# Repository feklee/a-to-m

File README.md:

Introduction
============

A-to-M is an experimental construction system: Atoms (*A*) are
assembled *to* form molecules (*M*).

A molecule is powered with a USB-C adapter. This adapter is also used
to program individual atoms.

Design guidelines
=================

For areas without solder mask, don’t use components smaller than 0603
and don’t put traces too close. A clearance of 0.35 mm is good.

MiniCore
========

For a good experience, i.e. fast power up of an atom upon connection,
install [MiniCore][1] as boot loader.

Examples
========

Atomic tree
-----------

Sequencer
---------

[][2]  
[Video][2]

License
=======

Except where noted otherwise, files are licensed under the WTFPL.

Copyright © 2020 [Felix E. Klee](felix.klee@inka.de)

This work is free. You can redistribute it and/or modify it under the
terms of the Do What The Fuck You Want To Public License, Version 2,
as published by Sam Hocevar. See the COPYING file for more details.

[1]: https://github.com/MCUdude/MiniCore
[2]: https://archive.org/details/a-to-m-sequencer

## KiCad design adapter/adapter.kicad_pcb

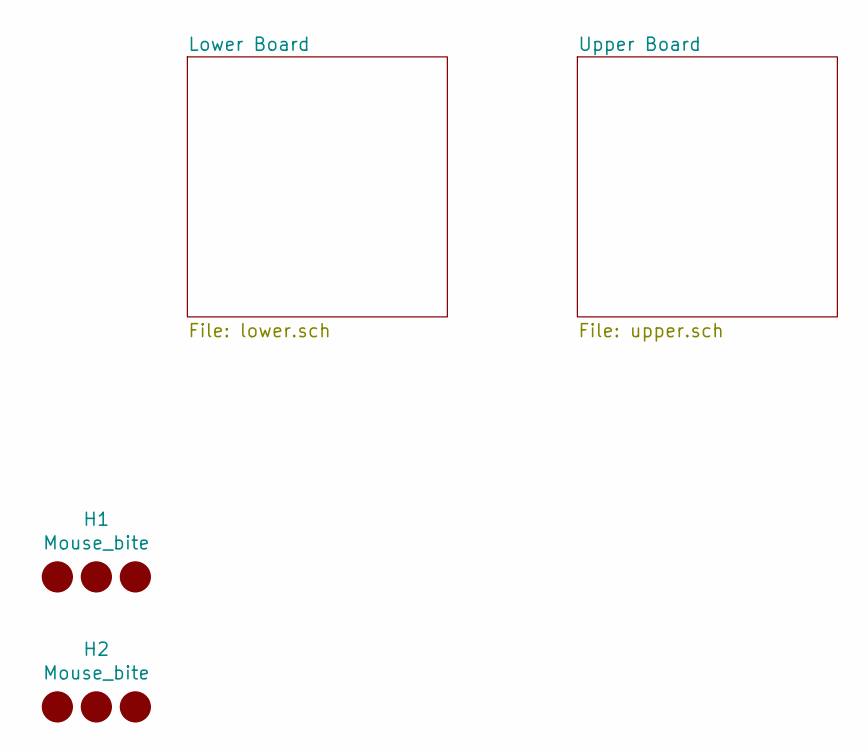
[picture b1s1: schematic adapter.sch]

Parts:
H1, H2: Mouse_bite; single_sided_tab_5mm

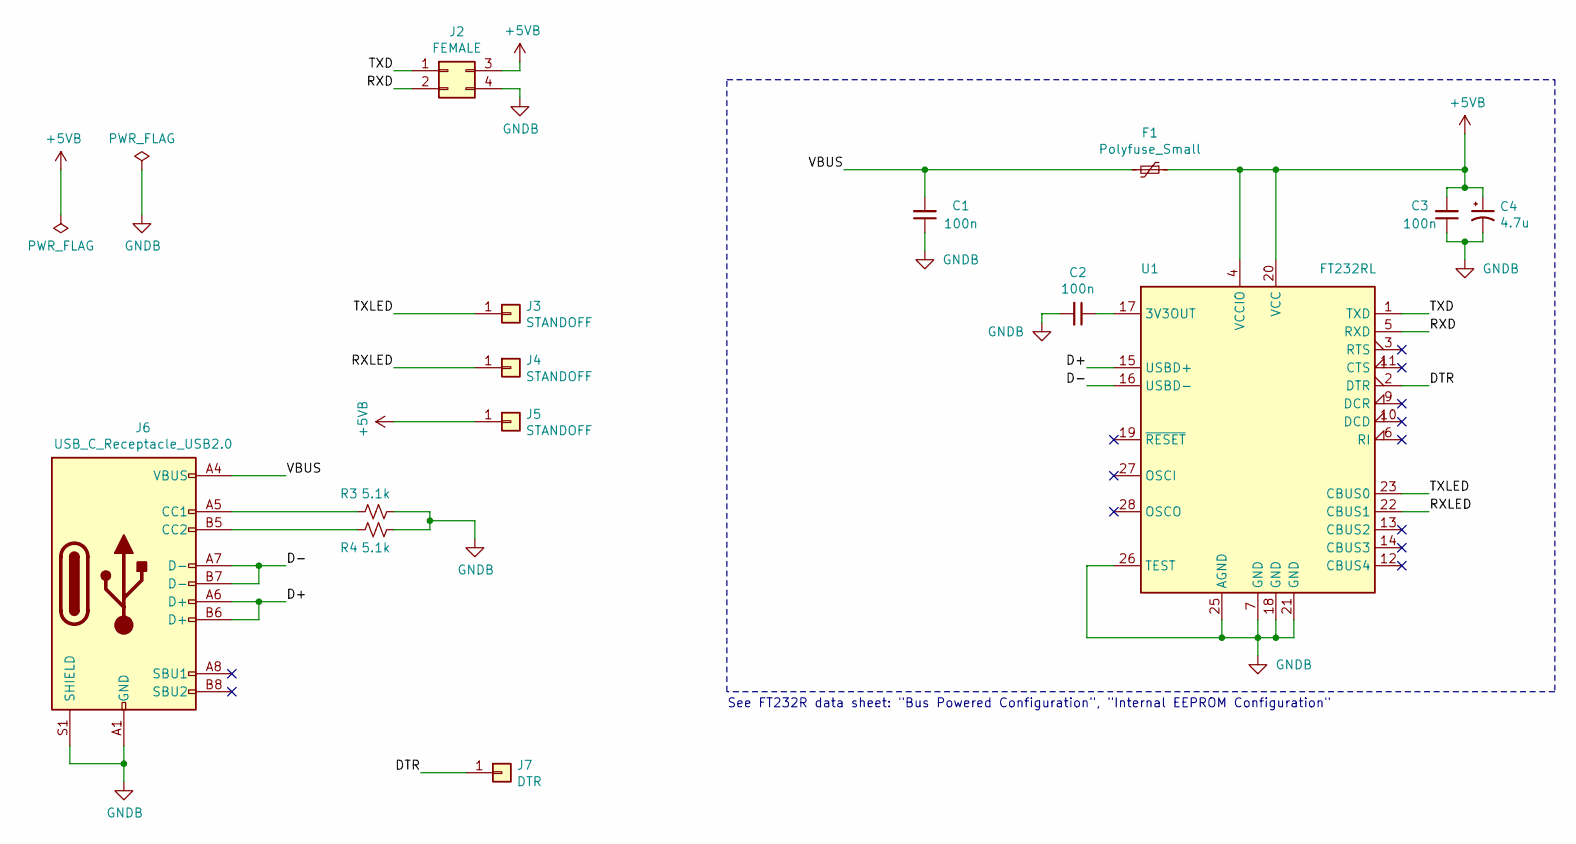
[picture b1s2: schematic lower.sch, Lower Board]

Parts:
C1, C2, C3: 100n; C_0805_2012Metric_Pad1.15x1.40mm_HandSolder
C4: 4.7u; C_0805_2012Metric_Pad1.15x1.40mm_HandSolder
F1: Polyfuse_Small; Fuse_1206_3216Metric_Pad1.42x1.75mm_HandSolder
J2: FEMALE; PinSocket_2x02_P2.54mm_Horizontal
J3, J4, J5: STANDOFF; MountingHole_2.2mm_M2_Pad_Via
J6: USB_C_Receptacle_USB2.0; SOFNG_MC-311D
J7: DTR; PinHeader_1x01_P2.54mm_Vertical
R3, R4: 5.1k; R_0805_2012Metric_Pad1.20x1.40mm_HandSolder
U1: FT232RL; SSOP-28_5.3x10.2mm_P0.65mm

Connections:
+5VB: C3.2, C4.1, F1.1, J2.3, J5.1, U1.4 (VCCIO), U1.20 (VCC)
/Lower Board/D+: J6.A6 (D+), J6.B6 (D+), U1.15 (USBD+)
/Lower Board/D-: J6.A7 (D-), J6.B7 (D-), U1.16 (USBD-)
/Lower Board/DTR: J7.1, U1.2 (DTR)
/Lower Board/RXD: J2.2, U1.5 (RXD)
/Lower Board/RXLED: J4.1, U1.22 (CBUS1)
/Lower Board/TXD: J2.1, U1.1 (TXD)
/Lower Board/TXLED: J3.1, U1.23 (CBUS0)
/Lower Board/VBUS: C1.2, F1.2, J6.A4 (VBUS), J6.A9 (VBUS), J6.B4 (VBUS), J6.B9 (VBUS)
GNDB: C1.1, C2.2, C3.1, C4.2, J2.4, J6.A1 (GND), J6.A12 (GND), J6.B1 (GND), J6.B12 (GND), J6.S1 (SHIELD), R3.1, R4.1, U1.7 (GND), U1.18 (GND), U1.21 (GND), U1.25 (AGND), U1.26 (TEST)
unnamed: C2.1, U1.17 (3V3OUT)
unnamed: J6.A5 (CC1), R3.2
unnamed: J6.B5 (CC2), R4.2

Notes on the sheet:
See FT232R data sheet: "Bus Powered Configuration", "Internal EEPROM Configuration"

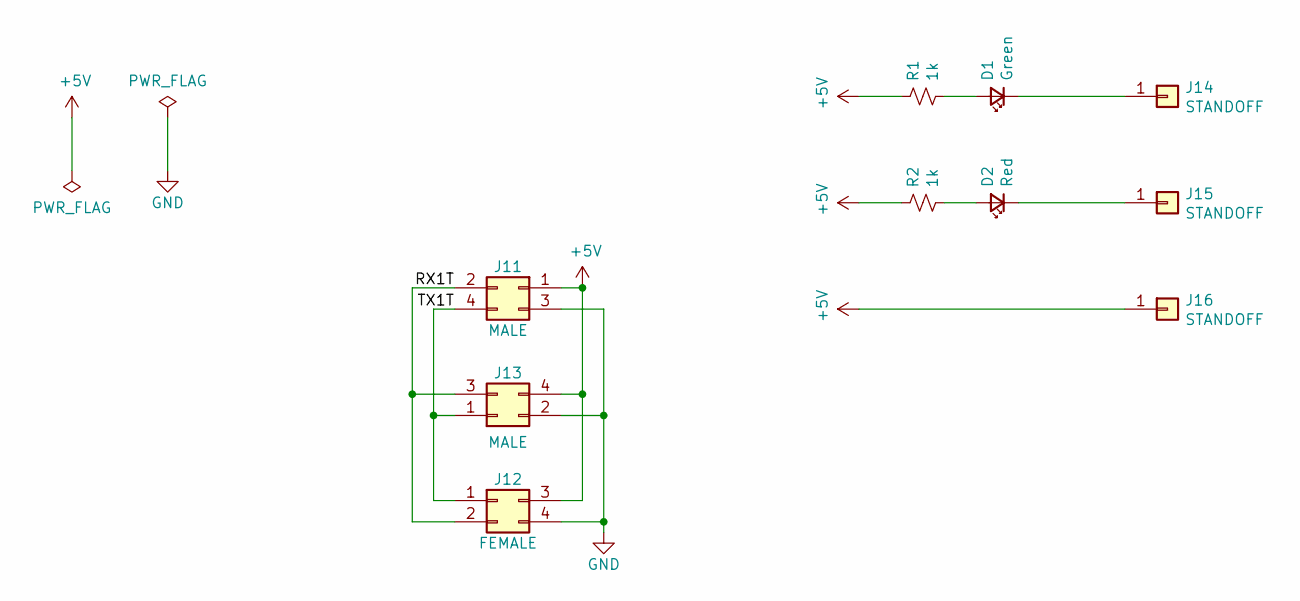
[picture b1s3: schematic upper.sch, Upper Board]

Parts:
D1: Green; LED_0805_2012Metric_Pad1.15x1.40mm_HandSolder
D2: Red; LED_0805_2012Metric_Pad1.15x1.40mm_HandSolder
J11, J13: MALE; PinHeader_2x02_P2.54mm_Horizontal
J12: FEMALE; PinSocket_2x02_P2.54mm_Horizontal
J14, J15, J16: STANDOFF; MountingHole_2.2mm_M2_Pad_Via
R1, R2: 1k; R_0805_2012Metric_Pad1.20x1.40mm_HandSolder

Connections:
+5V: J11.1, J12.3, J13.4, J16.1, R1.1, R2.1
/Upper Board/RX1T: J11.2, J12.2, J13.3
/Upper Board/TX1T: J11.4, J12.1, J13.1
GND: J11.3, J12.4, J13.2
unnamed: D1.1 (K), J14.1
unnamed: D1.2 (A), R1.2
unnamed: D2.1 (K), J15.1
unnamed: D2.2 (A), R2.2

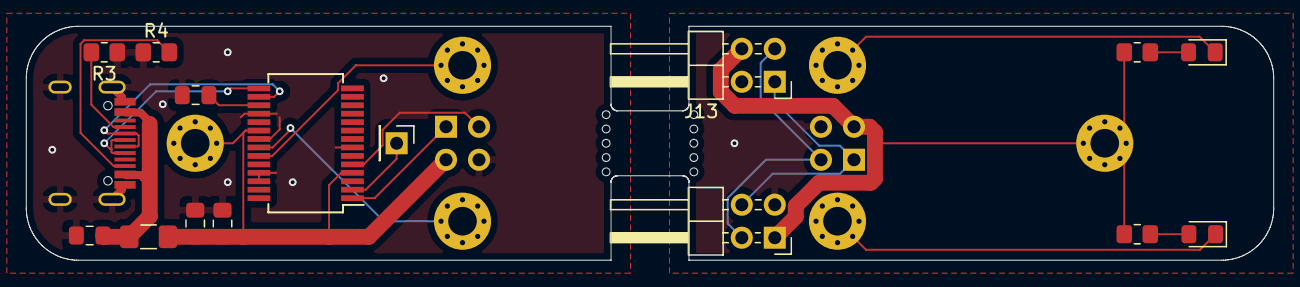
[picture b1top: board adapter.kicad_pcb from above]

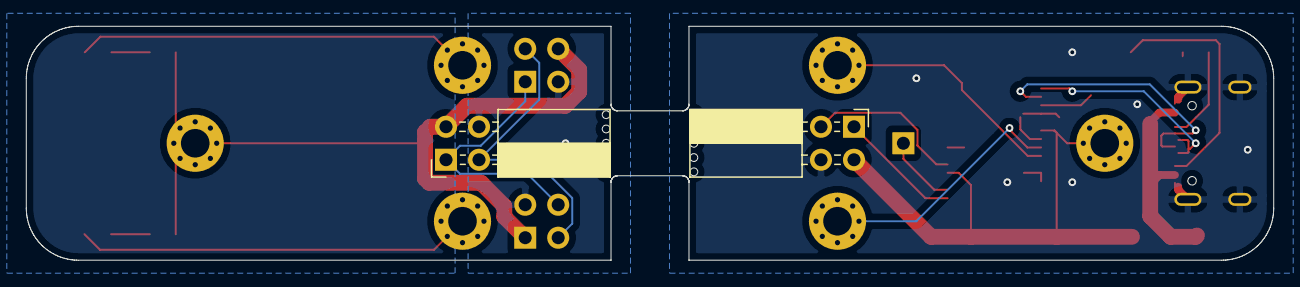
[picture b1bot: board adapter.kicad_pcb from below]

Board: 2 copper layers, 96.0 x 18.0 mm, 26 parts (2 on the bottom side), 21 nets.

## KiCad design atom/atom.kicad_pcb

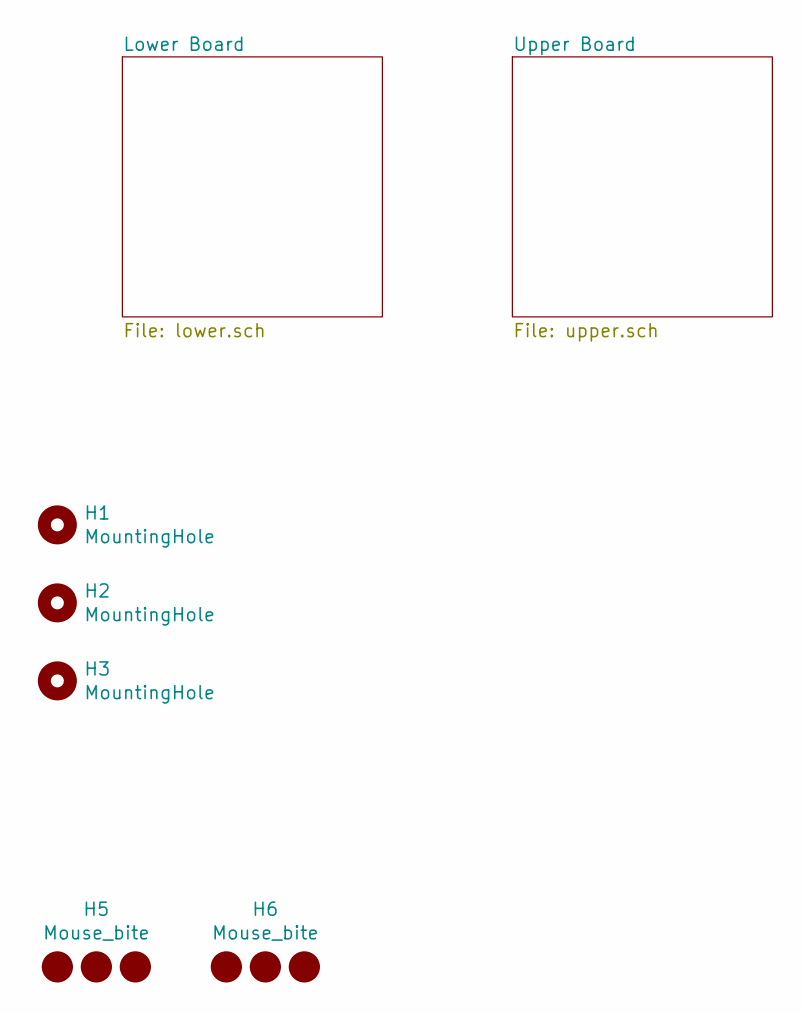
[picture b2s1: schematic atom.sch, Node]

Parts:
H1, H2, H3: MountingHole; JLCPCB-tooling-hole; JLCPCB BOM False
H5, H6: Mouse_bite; single_sided_tab_5mm; JLCPCB BOM False

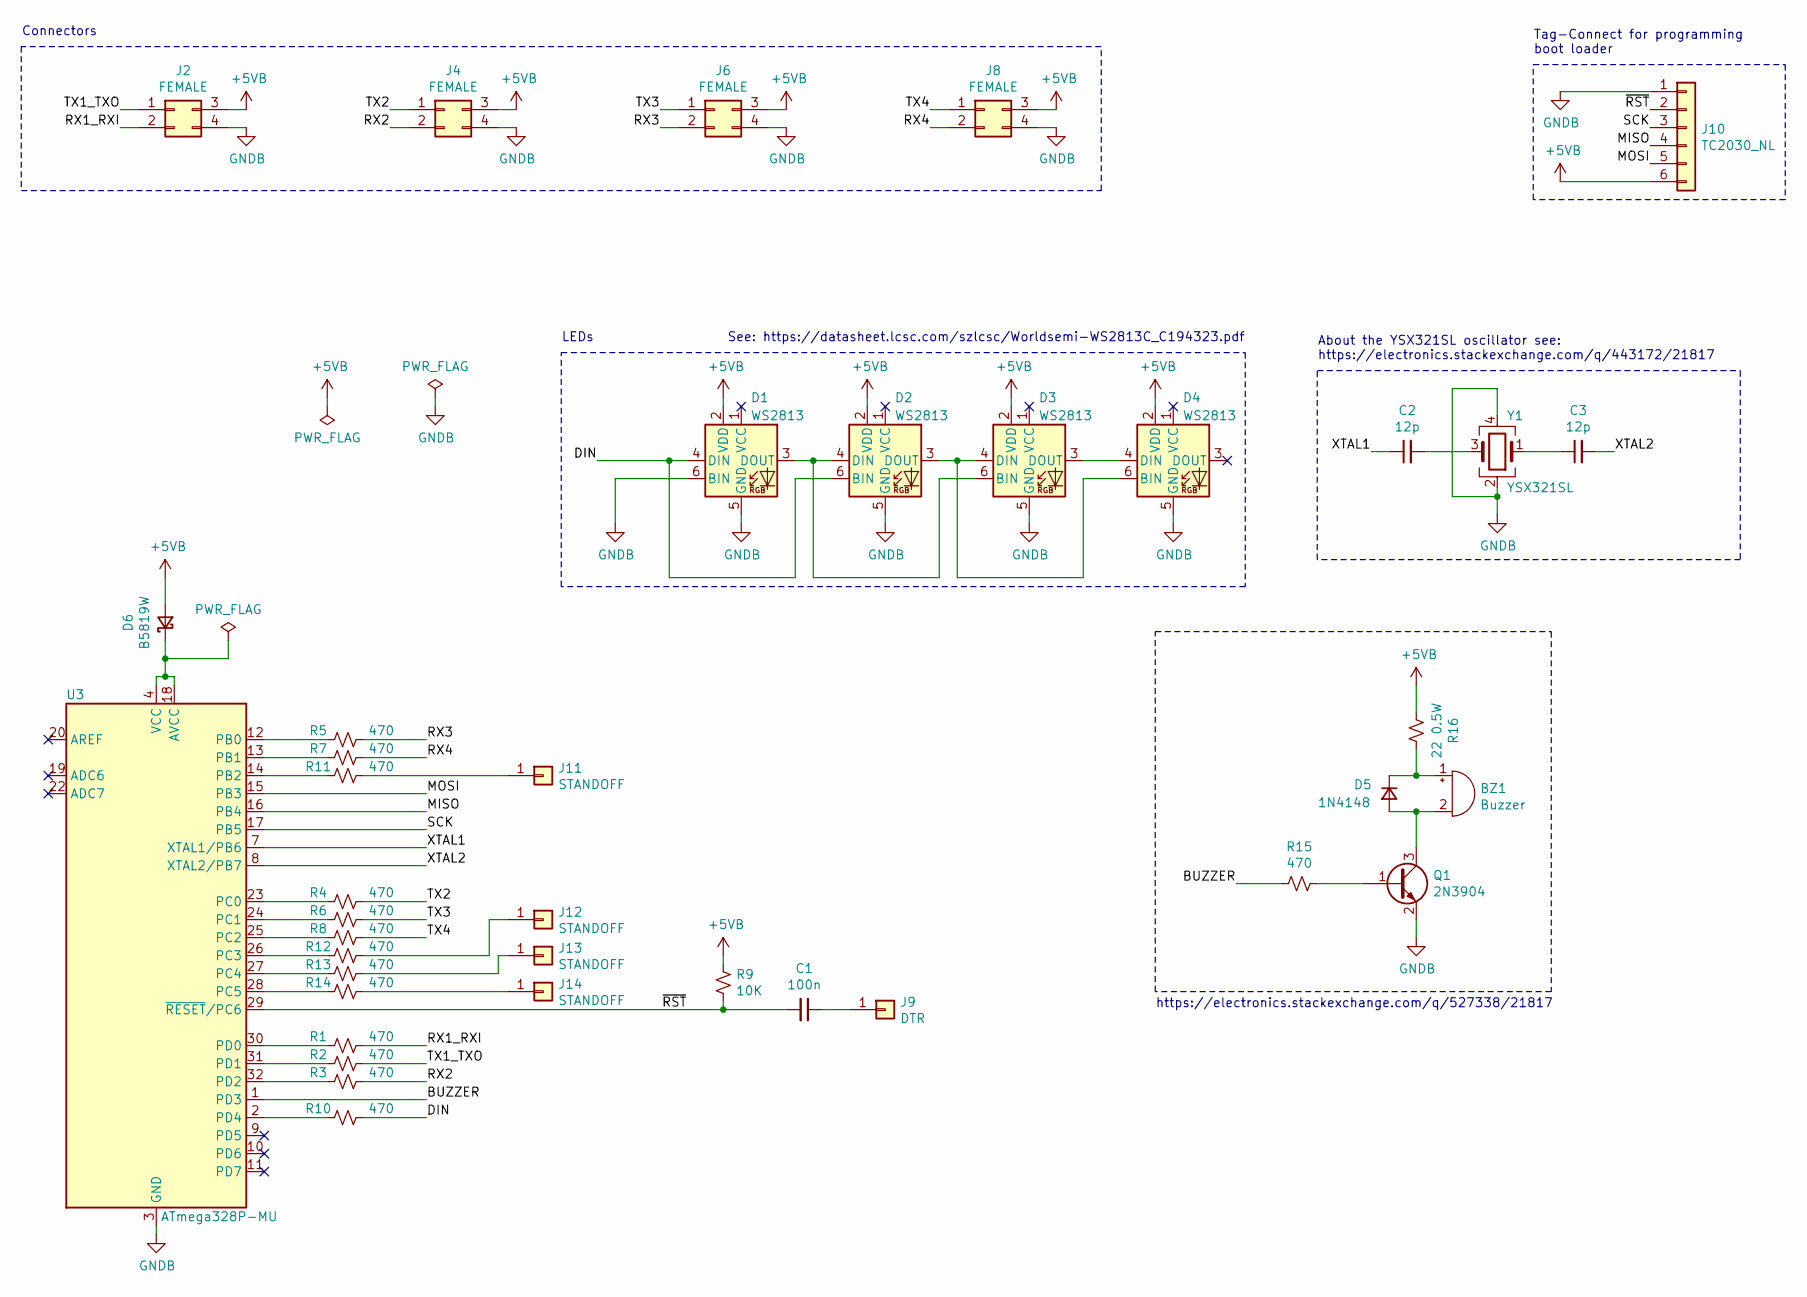
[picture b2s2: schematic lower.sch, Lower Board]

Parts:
BZ1: Buzzer; MLT-5020; MPN MLT-5020; LCSC Part C94598
C1: 100n; C_0402_1005Metric; MPN CL05B104KO5NNNC; LCSC Part C1525
C2, C3: 12p; C_0402_1005Metric; MPN 0402CG120J500NT; LCSC Part C1547
D1, D2, D3, D4: WS2813; bottom-leaf; MPN WS2813C; LCSC Part C194323
D5: 1N4148; D_SOD-323; MPN 1N4148WS-7-F; LCSC Part C60580
D6: B5819W; D_SOD-123
J2, J4, J6, J8: FEMALE; PinSocket_2x02_P2.54mm_Horizontal; MPN A2541HWR-2x2P; LCSC Part C239353
J9: DTR; PinHeader_1x01_P2.54mm_Vertical; JLCPCB BOM False
J10: TC2030_NL; Tag-Connect_TC2030-IDC-NL_2x03_P1.27mm_Vertical; JLCPCB BOM False
J11, J12, J13, J14: STANDOFF; MountingHole_2.2mm_M2_Pad_Via; JLCPCB BOM False
Q1: 2N3904; SOT-23; MPN PMBT3904,215; LCSC Part C8667
R1, R2, R3, R4, R5, R6, R7, R8, R10, R11, R12, R13, R14, R15: 470; R_0402_1005Metric; MPN 0402WGF4700TCE; LCSC Part C25117
R9: 10K; R_0402_1005Metric; MPN 0402WGF1002TCE; LCSC Part C25744
R16: 22 0.5W; R_2010_5025Metric; MPN 2010W2F220JT4S; LCSC Part C70404
U3: ATmega328P-MU; QFN-32-1EP_5x5mm_P0.5mm_EP3.1x3.1mm; MPN ATMEGA328P-MU; LCSC Part C783592
Y1: YSX321SL; MPN X322516MOB4SI; LCSC Part C12668

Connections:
+5VB: D1.2 (VDD), D2.2 (VDD), D3.2 (VDD), D4.2 (VDD), D6.2 (A), J2.3, J4.3, J6.3, J8.3, J10.6, R9.1, R16.2
/Lower Board/BUZZER: R15.2, U3.1 (PD3)
/Lower Board/DIN: D1.4 (DIN), D2.6 (BIN), R10.1
/Lower Board/MISO: J10.4, U3.16 (PB4)
/Lower Board/MOSI: J10.5, U3.15 (PB3)
/Lower Board/RX1_RXI: J2.2, R1.1
/Lower Board/RX2: J4.2, R3.1
/Lower Board/RX3: J6.2, R5.1
/Lower Board/RX4: J8.2, R7.1
/Lower Board/SCK: J10.3, U3.17 (PB5)
/Lower Board/TX1_TXO: J2.1, R2.1
/Lower Board/TX2: J4.1, R4.1
/Lower Board/TX3: J6.1, R6.1
/Lower Board/TX4: J8.1, R8.1
/Lower Board/XTAL1: C2.1, U3.7 (XTAL1/PB6)
/Lower Board/XTAL2: C3.2, U3.8 (XTAL2/PB7)
/Lower Board/~RST: C1.2, J10.2, R9.2, U3.29 (~RESET~/PC6)
GNDB: D1.5 (GND), D1.6 (BIN), D2.5 (GND), D3.5 (GND), D4.5 (GND), J2.4, J4.4, J6.4, J8.4, J10.1, Q1.2 (E), U3.3 (GND), U3.5 (GND), U3.21 (GND), U3.33 (GND), Y1.2, Y1.4
unnamed: BZ1.1 (-), D5.1 (K), R16.1
unnamed: BZ1.2 (+), D5.2 (A), Q1.3 (C)
unnamed: C1.1, J9.1
unnamed: C2.2, Y1.3
unnamed: C3.1, Y1.1
unnamed: D1.3 (DOUT), D2.4 (DIN), D3.6 (BIN)
unnamed: D2.3 (DOUT), D3.4 (DIN), D4.6 (BIN)
unnamed: D3.3 (DOUT), D4.4 (DIN)
unnamed: D6.1 (K), U3.4 (VCC), U3.6 (VCC), U3.18 (AVCC)
unnamed: J11.1, R11.1
unnamed: J12.1, R12.1
unnamed: J13.1, R13.1
unnamed: J14.1, R14.1
unnamed: Q1.1 (B), R15.1
unnamed: R1.2, U3.30 (PD0)
unnamed: R2.2, U3.31 (PD1)
unnamed: R3.2, U3.32 (PD2)
unnamed: R4.2, U3.23 (PC0)
unnamed: R5.2, U3.12 (PB0)
unnamed: R6.2, U3.24 (PC1)
unnamed: R7.2, U3.13 (PB1)
unnamed: R8.2, U3.25 (PC2)
unnamed: R10.2, U3.2 (PD4)
unnamed: R11.2, U3.14 (PB2)
unnamed: R12.2, U3.26 (PC3)
unnamed: R13.2, U3.27 (PC4)
unnamed: R14.2, U3.28 (PC5)

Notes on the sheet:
See: https://datasheet.lcsc.com/szlcsc/Worldsemi-WS2813C_C194323.pdf
LEDs
Connectors
About the YSX321SL oscillator see: https://electronics.stackexchange.com/q/443172/21817
Tag-Connect for programming boot loader
https://electronics.stackexchange.com/q/527338/21817

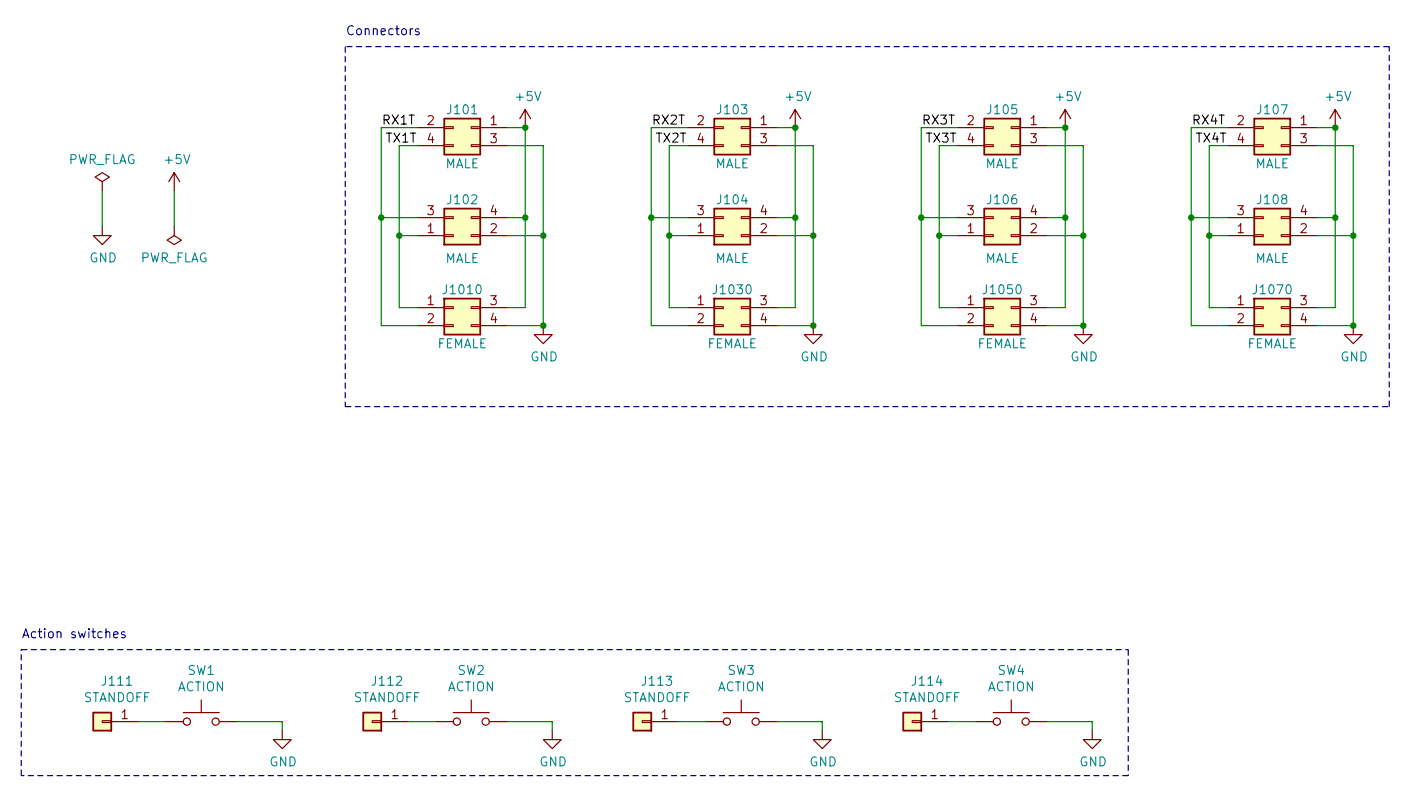
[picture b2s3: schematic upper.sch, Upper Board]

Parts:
J101, J103, J105, J107, J1010, J1030, J1050, J1070: MALE; PinHeader_2x02_P2.54mm_Horizontal; MPN A2541WR-2x2P; LCSC Part C239333
J102, J104, J106, J108: FEMALE; PinSocket_2x02_P2.54mm_Horizontal; MPN A2541HWR-2x2P; LCSC Part C239353
J111, J112, J113, J114: STANDOFF; MountingHole_2.2mm_M2_Pad_Via; JLCPCB BOM False
SW1, SW2, SW3, SW4: ACTION; top-leaf; MPN TS-1187A-B-A-B; LCSC Part C318884

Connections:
+5V: J101.1, J102.3, J103.1, J104.3, J105.1, J106.3, J107.1, J108.3, J1010.4, J1030.4, J1050.4, J1070.4
/Upper Board/RX1T: J101.2, J102.2, J1010.3
/Upper Board/RX2T: J103.2, J104.2, J1030.3
/Upper Board/RX3T: J105.2, J106.2, J1050.3
/Upper Board/RX4T: J107.2, J108.2, J1070.3
/Upper Board/TX1T: J101.4, J102.1, J1010.1
/Upper Board/TX2T: J103.4, J104.1, J1030.1
/Upper Board/TX3T: J105.4, J106.1, J1050.1
/Upper Board/TX4T: J107.4, J108.1, J1070.1
GND: J101.3, J102.4, J103.3, J104.4, J105.3, J106.4, J107.3, J108.4, J1010.2, J1030.2, J1050.2, J1070.2, SW1.2, SW2.2, SW3.2, SW4.2
unnamed: J111.1, SW1.1
unnamed: J112.1, SW2.1
unnamed: J113.1, SW3.1
unnamed: J114.1, SW4.1

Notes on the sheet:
Action switches
Connectors

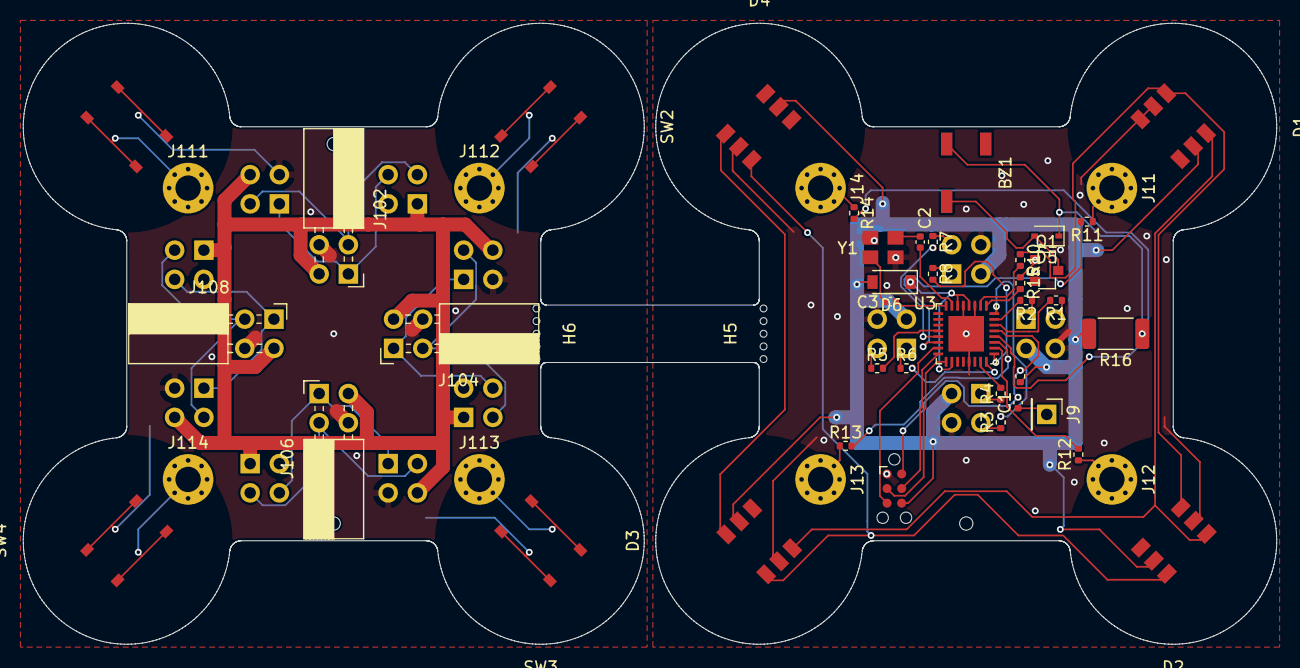
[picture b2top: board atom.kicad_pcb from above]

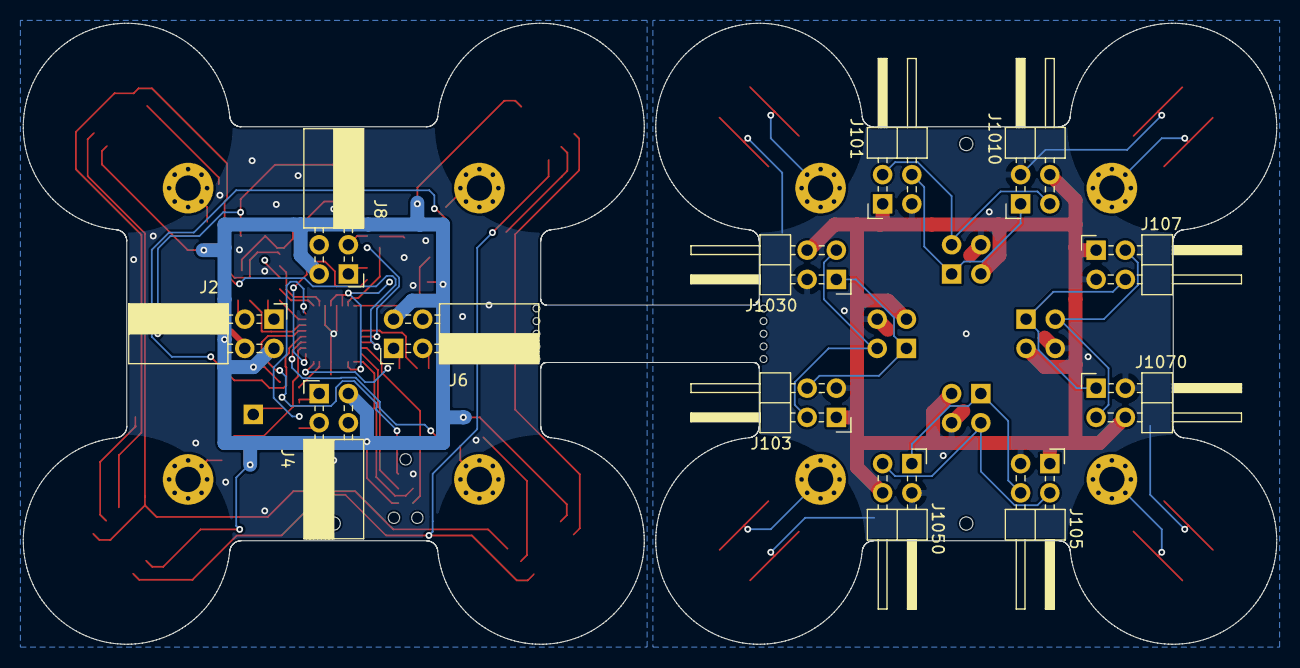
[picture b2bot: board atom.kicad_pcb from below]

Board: 2 copper layers, 109.0 x 54.0 mm, 64 parts (12 on the bottom side), 59 nets.

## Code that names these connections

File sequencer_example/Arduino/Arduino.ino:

#include <FastLED.h>
#include <ezButton.h>

constexpr uint8_t buttonPinNos[] = {
  10, // PB2
  17, // PC3
  18, // PC4
  19 // PC5
};

// This code is for RX and TX not being crossed over. (design bug in
// the board, but fixed since)
constexpr uint8_t communicationPinNos[] = {
  0, // RX1 = PD0 = PCINT16
  2, // RX2 = PD2 = PCINT18
  8, // RX3 = PB0 = PCINT0
  9 // RX4 = PB1 = PCINT1
};

constexpr uint8_t speakerPinNo = 3;

#define LED_PIN     4
#define NUM_LEDS    4
#define BRIGHTNESS  255
#define LED_TYPE    WS2813
#define COLOR_ORDER GRB
CRGB leds[NUM_LEDS];
uint8_t hues[NUM_LEDS];
volatile bool pulseHasBeenReceived = false;
volatile uint8_t commPinThatReceivedPulse;

bool waitingForMultiButtonRelease = false;

constexpr uint8_t noOfDurations = 3;
uint16_t durations[noOfDurations] = { // in ms
  125,
  250,
  375
};
int8_t selectedDurationIndex = 1;

constexpr uint8_t noOfNotes = 14;
uint16_t frequencies[noOfNotes] = {
  2093, // C7
  2349, // D7
  2637, // E7
  2794, // F7
  3136, // G7
  3520, // A7
  3951, // B7
  4186, // C8
  4699, // D8
  5274, // E8
  5588, // F8
  6272, // G8
  7040, // A8
  7902 // B8
};
uint8_t selectedNote = 7;

constexpr uint8_t noOfWaveForms = 3;
struct {
  enum {silent, square, noise};
} waveForms;
uint8_t selectedWaveForm = waveForms.square;

struct {
  enum {incNote, duration, decNote, waveForm};
} buttonNos;

ezButton buttons[] = {
  {buttonPinNos[0]},
  {buttonPinNos[1]},
  {buttonPinNos[2]},
  {buttonPinNos[3]}
};

uint16_t toggleCount;

void blinkLed(uint8_t i) {
  leds[i].setHSV(255, 0, 255);
  FastLED.show();
  delay(100);
  leds[i].setHSV(255, 0, 0);
  FastLED.show();
}

uint8_t nextDurationIndex() {
  return (selectedDurationIndex + 1) % noOfDurations;
}

uint8_t prevNote() {
  return selectedNote == 0 ? 0 : selectedNote - 1;
}

uint8_t nextNote() {
  return selectedNote == noOfNotes - 1
    ? noOfNotes - 1
    : selectedNote + 1;
}

uint8_t nextWaveForm() {
  return (selectedWaveForm + 1) % noOfWaveForms;
}

CHSV noteColor(uint8_t note) {
  const uint8_t maxNote = noOfNotes - 1;
  return CHSV(uint32_t(note) * 64 / maxNote, 255, 255);
}

CHSV durationColor(uint8_t durationIndex) {
  const uint8_t maxDurationIndex = noOfDurations - 1;
  return CHSV(160 + uint32_t(durationIndex) * 96 / maxDurationIndex,
              255, 255);
}

CHSV waveFormColor(uint8_t waveForm) {
  switch (waveForm) {
  case waveForms.square:
    return CHSV(96, 255, 255);
  case waveForms.noise:
    return CHSV(0, 0, 255);
  case waveForms.silent:
  default:
    return CHSV(0, 0, 0);
  }
}

void showStatusWithLeds() {
  leds[buttonNos.incNote] = noteColor(nextNote());
  leds[buttonNos.decNote] = noteColor(prevNote());
  leds[buttonNos.duration] = durationColor(selectedDurationIndex);
  leds[buttonNos.waveForm] = waveFormColor(selectedWaveForm);
  
  FastLED.show();
}

void blinkAllLeds() {
  for (uint8_t i = 0; i < 4; i ++) {
    leds[i].setHSV(255, 0, 255);
  }
  FastLED.show();
  delay(250);
  showStatusWithLeds();
}

inline void parseSignal(const uint8_t minPinNo,
                        const uint8_t maxPinNo) {
  for (uint8_t i = 0; i < 4; i ++) {
    const uint8_t communicationPinNo = communicationPinNos[i];
    if (communicationPinNo >= minPinNo &&
        communicationPinNo <= maxPinNo) {
      if (digitalRead(communicationPinNo) == 0) {
        pulseHasBeenReceived = true;
        commPinThatReceivedPulse = i;
        break;
      }
    }
  }
}

ISR(PCINT2_vect) { // D0-D7
  parseSignal(0, 7);
}

ISR(PCINT0_vect) { // D8-D13
  parseSignal(8, 13);
}

void sendPulseOnCommunicationPin(uint8_t i) {
  uint8_t communicationPinNo = communicationPinNos[i];
  disablePinChangeInterrupts();
  pinMode(communicationPinNo, OUTPUT);
  digitalWrite(communicationPinNo, LOW);
  delay(10);
  digitalWrite(communicationPinNo, HIGH);
  pinMode(communicationPinNo, INPUT_PULLUP);
  enablePinChangeInterrupts();
}

void enablePinChangeInterrupts() {
  PCICR = // Pin Change Interrupt Control Register
    bit(PCIE2) | // PCINT16 to PCINT23
    bit(PCIE0); // PCINT0 to PCINT7
  PCMSK2 = 0;
  bitWrite(PCMSK2, PCINT18, 1);
  bitWrite(PCMSK2, PCINT16, 1);
  PCMSK0 = 0;
  bitWrite(PCMSK0, PCINT1, 1);
  bitWrite(PCMSK0, PCINT0, 1);
}

void disablePinChangeInterrupts() {
  PCICR = 0;
  PCMSK2 = 0;
  PCMSK0 = 0;
}

void listenOnCommunicationPins() {
  for (uint8_t i = 0; i < 4; i++) {
    pinMode(communicationPinNos[i], INPUT_PULLUP);
  }
}

void sendPulseOnOtherCommPins(const uint8_t pinNotToPulse) {
  for (uint8_t i = 0; i < 4; i++) {
    if (i != pinNotToPulse) {
      sendPulseOnCommunicationPin(i);
    }
  }
}

void sendPulseOnAllCommPins() {
  sendPulseOnOtherCommPins(4);
}

// Taken from (and edited):
// https://github.com/ninetreesdesign/randomNumberGenerator
uint16_t rng() {
  static uint16_t y = 0;
  y += (micros() && 0x1FFF); // seeded with changing number
  y ^= y << 2;
  y ^= y >> 7;
  y ^= y << 7;
  return y;
}

ISR(TIMER1_COMPA_vect) {
  if (toggleCount > 0) {
    switch (selectedWaveForm) {
    case waveForms.square:
      PORTD ^= 0b00001000;
      break;
    case waveForms.noise:
      if (rng() & 1) {
        PORTD ^= 0b00001000;
      }
      break;
    }
    toggleCount--;
  } else {
    stopSound();
  }
}

void stopSound() {
  TIMSK1 = 0;
  PORTD &= 0b11110111; // Seen in Arduino tone(), maybe not necessary
}

void playSound(
               uint16_t frequency, // Hz
               uint16_t duration // ms
               ) {
  cli(); // Disable interrupts till everything is configured

  // Timer 1 is a 16-bit timer.

  // Set WGM - Waveform Generation Mode - to CTC (Clear Timer on
  // Compare Match, TOP = OCR1A):
  bitWrite(TCCR1B, WGM13, 0);
  bitWrite(TCCR1B, WGM12, 1);
  bitWrite(TCCR1A, WGM11, 0);
  bitWrite(TCCR1A, WGM10, 0);

  // Disable prescaler:
  bitWrite(TCCR1B, CS12, 0);
  bitWrite(TCCR1B, CS11, 0);
  bitWrite(TCCR1B, CS10, 1);

  // Define how often to call the interrupt:
  OCR1A = F_CPU / frequency / 2;

  // Make ISR(TIMER2_COMPA_vect) be called when timer reaches TOP:
  bitWrite(TIMSK1, OCIE1A, 1);

  toggleCount = 2ul * frequency * duration / 1000;

  sei();
}

void playSelectedSound() {
  playSound(frequencies[selectedNote],
            durations[selectedDurationIndex]);
}

void debounceButtons() {
  for (uint8_t i = 0; i < 4; i++) {
    buttons[i].setDebounceTime(50);
  }
}

void setup() {
  FastLED.addLeds<LED_TYPE, LED_PIN, COLOR_ORDER>(leds, NUM_LEDS).
    setCorrection(TypicalLEDStrip);
  FastLED.setBrightness(BRIGHTNESS);
  showStatusWithLeds();

  debounceButtons();

  listenOnCommunicationPins();
  enablePinChangeInterrupts();
}

void loopButtons() {
  for (uint8_t i = 0; i < 4; i++) {
    buttons[i].loop();
  }
}

uint8_t noOfButtonsPressed() {
  uint8_t no = 0;
  for (uint8_t i = 0; i < 4; i++) {
    if (buttons[i].getState() == LOW) {
      no++;
    }
  }
  return no;
}

bool multipleButtonsHaveBeenReleased() {
  if (!waitingForMultiButtonRelease) {
    if (noOfButtonsPressed() > 1) {
      waitingForMultiButtonRelease = true;
    }
    return false;
  }

  if (noOfButtonsPressed() == 0) {
    waitingForMultiButtonRelease = false;
    return true;
  }

  return false;
}

void parseSingleButtonReleases() {
  bool aButtonHasBeenReleased = false;

  if (buttons[buttonNos.incNote].isReleased()) {
    selectedNote = prevNote();
    aButtonHasBeenReleased = true;
  }

  if (buttons[buttonNos.decNote].isReleased()) {
    selectedNote = nextNote();
    aButtonHasBeenReleased = true;
  }

  if (buttons[buttonNos.duration].isReleased()) {
    selectedDurationIndex = nextDurationIndex();
    aButtonHasBeenReleased = true;
  }

  if (buttons[buttonNos.waveForm].isReleased()) {
    selectedWaveForm = nextWaveForm();
    aButtonHasBeenReleased = true;
  }

  if (aButtonHasBeenReleased) {
    showStatusWithLeds();
    playSelectedSound();
  }
}

void parseButtons() {
  if (multipleButtonsHaveBeenReleased()) {
    sendPulseOnAllCommPins();
    return;
  }

  if (waitingForMultiButtonRelease) {
    return;
  }

  parseSingleButtonReleases();
}

void loop() {
  if (pulseHasBeenReceived) {
    playSelectedSound();
    blinkAllLeds();
    sendPulseOnOtherCommPins(commPinThatReceivedPulse);
    pulseHasBeenReceived = false;
  }

  loopButtons();
  parseButtons();
}

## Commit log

2020-10-13 Add WIP
2020-10-13 Add picture of mockup
2020-10-13 Add footprints
2020-10-13 Assign footprints and complete BOM
2020-10-13 Place footprints
2020-10-14 Add buzzer and clean up
2020-10-16 Add footprint for switch
2020-10-16 Iterate
2020-10-16 Precisely position some components
2020-10-16 Create layout for KiCad
2020-10-16 Select transistor for buzzer
2020-10-16 Fix: Wrong footprint for transistor
2020-10-16 Fix: Missing and conflicting values in symbol table
2020-10-16 Add footprint for diode
2020-10-16 Add footprint for buzzer
2020-10-16 Assign footprints
2020-10-16 Arrange components
2020-10-21 Play with shape / design
2020-10-21 Give project more mature name
2020-10-21 Update solder mask keep out
2020-10-21 Ignore Gerbers
2020-10-21 Add copper pour keep-out zones for top board
2020-10-22 Route top board
2020-10-22 Add +5V network
2020-10-22 Reduce footprint of tab
2020-10-22 Ignore FreeCad backup files
2020-10-22 Add design guidelines
2020-10-22 Add power network
2020-10-22 Switch to WS2813C (bigger footprint)
2020-10-22 Create footprint for bottom leaf (w/ WS2813)
2020-10-22 Assign bottom-leaf footprints to LEDs
2020-10-22 Position bottom-leaf footprints
2020-10-22 Round power for bottom
2020-10-22 Route top board (but DRC errors)
2020-10-22 Fix: overlapping fill zones
2020-10-22 Remove conflicting track
2020-10-22 Fix: Unconnected GND
2020-10-22 Fix: unconnected fill zones
2020-10-22 Fix: Track too close to via
2020-10-22 Fix: Drill holes in mouse bite too close
2020-10-28 Fix: Tag-Connect cannot be pushed through holes
2020-10-28 Fix: Small resistor not in solder mask area
2020-10-29 Move holes for headers 0.1 mm inwards
2020-10-29 Make Tag-Connect easier accessible
2020-10-29 Fix: DRC errors
2020-10-29 gerber -> gerbers
2020-10-29 Update Gerber settings
2020-10-30 Rename top/bottom to avoid confusion with layers
2020-10-30 Resize sheets for consistency
2020-10-30 Add schematic for adapter
2020-10-30 Add resettable fuse (don’t connect yet)
2020-10-30 Remove backup files
2020-10-30 Remove cache
2020-10-30 Ignore certain KiCad files
2020-10-30 Fix: Nested redundancy
2020-11-03 Optimize resistor
2020-11-03 Route new resistor package
2020-11-03 Experiment: Add text to label buttons
2020-11-03 Experimental: Change button labels to dots
2020-11-04 Readd previous labels
2020-11-05 Fix: Wrong pad numbering
2020-11-05 Retrace to accommodate for changed footprint
2020-11-05 Annotate pins
2020-11-05 Fix: Wrong pin order
2020-11-05 Fix: Wrong labels
2020-11-06 Reroute, add my chop
2020-11-06 Remove outdated user drawings
2020-11-06 Reroute
2020-11-06 Move TX3/RX3 resistors closer to pin holes
2020-11-06 Move RX2/TX2 closer to respective holes
2020-11-06 Make space for chop
2020-11-06 Swap sides to move mouse bites in safer position
2020-11-06 Fix DRC errors
2020-11-06 Swap sides, update edge cuts
2020-11-06 15 → 22 Ω for safety and to avoid clipping
2020-11-06 Fix: Wrong pin order in upper board
2020-11-06 Fix: UIDs of connectors changed
2020-11-06 Retrace upper board
2020-11-06 Change to parts available for JLCPCB PCBA
2020-11-06 Fix: Wrong fabrication attributes
2020-11-06 Add JLCPCB tooling hole
2020-11-06 Incorporate JLCPCB tooling holes
2020-11-06 Fix: Non connected GNDB areas
2020-11-07 Hide tooling holes under female headers
2020-11-07 Flip FTDI connector inward for protection
2020-11-07 Model new board edge cuts in 3D
2020-11-10 Make fields compatible with JLCPCB BOM plugin
2020-11-10 Update footprints (some falsely not marked as SMD)
2020-11-11 Create JLCPCB compatible breakaway tab
2020-11-12 Optimize
2020-11-12 Insert wider mouse bites to match JLCPCB capabil.
2020-11-12 Add tooling holes to schematic
2020-11-12 Create symbol for mouse bite
2020-11-12 Add mouse bite
2020-11-12 Replace footprints without schematic symbol
2020-11-12 Modify outline for new mouse bites
2020-11-19 Finish schematic
2020-11-19 Rename for consistency
2020-11-19 Draft design for adapter
2020-11-19 Update view (unimportant)
2020-11-19 Move project spec. footprint library for sharing
2020-11-19 Point to project footprint library
2020-11-19 Add footprint for USB-C 2.0 receptacle
2020-11-19 Update holes and add shield connection
2020-11-19 Assign USB receptacle
2020-11-19 Add power flags
2020-11-19 Change female headers to horizontal
2020-11-19 Use 1206 pad for fuse
2020-11-19 Set clearance for holes
2020-11-19 Add missing pads for USB-C 2.0
2020-11-19 Put footprints on layout
2020-11-19 Set design rules
2020-11-19 No change, just update last update date
2020-11-19 Add holes for standoffs
2020-11-19 Design edge cuts
2020-11-19 Add edge cuts and roughly place components
2020-11-19 Model in 3D and define positions
2020-11-19 Define positions of additional standoffs
2020-11-19 Position connectors and standoff holes
2020-11-19 Define positions for LEDs
2020-11-19 Move LEDs to upper board
2020-11-19 Move LEDs to safer place
2020-11-19 Annotate
2020-11-19 Update footprints
2020-11-19 Share project specific symbol library
2020-11-19 Make project specific symbol library available
2020-11-19 Add mouse bites
2020-11-19 Add footprints for mouse bites
2020-11-20 Use different power net names for lower board
2020-11-20 Finish routing
2020-11-20 Configure Gerber export options
2020-11-20 Move around component positions
2020-11-23 Add symbol for transistor used
2020-11-23 Fix: Wrong pin numbering of transistor
2020-11-23 Fix: Wrong pinout for transistor
2020-11-23 Change order of A-T-O-M
2020-11-25 Move around text on F.Fab layer
2020-11-25 Make interesting values visible on F.Fab
2020-11-26 Add 56k pullups to fake USB host signature
2020-11-26 Put +5V on standoff: Make LEDs work w/o connection
2020-11-26 Add power flags to pass DRC check
2020-11-26 Assign footprints to pullups
2020-11-26 Add new footprints, connect upper standoff
2020-11-26 Connect lower standoff
2020-11-26 Make pads longer for easier hand soldering
2020-11-26 Update USB receptacle footprint
2020-11-27 Finish routing following changes
2020-11-27 Hide mouse bites under female headers
2020-11-27 Save
2020-11-27 Specify and wire up Schottky diode
2020-11-27 Wire Schottky diode
2020-11-27 Optimize wiring
2020-11-27 Add temporary fix for: upper+lower not bridged
2020-11-28 Move all male headers to upper board
2020-11-28 Fix fix: Wrong wiring for new males
2020-12-02 Add mounting holes for PCBA
2020-12-03 Move values to make nicer print
2020-12-04 Fix: Adapter identif. as down- instead of upstream
2020-12-04 Reroute to reflect fix
2020-12-05 Ungroup
2020-12-05 Move male headers to upper board
2020-12-05 No change
2020-12-05 Create alternative upper adapter board as fix
2020-12-05 Change footprint(s)
2020-12-05 Update positions for new footprints + orientation
2020-12-05 Move footprints to exact positions
2020-12-08 Fix: Connectors on wrong side
2020-12-08 Trace
2020-12-08 Nothing
2020-12-09 Fix pinout
2020-12-09 Remove fix which is not needed anymore
2020-12-09 Fix bridging: Move male headers to upper board
2020-12-09 Add missing power flag
2020-12-09 Rewire
2020-12-09 Remove fix, after merging it in PCB
2020-12-09 Move back to original name
2020-12-09 The PCB is an atom
2020-12-10 Rewrite
2020-12-10 Improve readability
2020-12-10 Mention adapter
2020-12-10 Clean up and rename: PCB -> atom
2020-12-10 Add introduction to title
2020-12-11 Add copper pour for aesthetic reasons
2020-12-11 Fix: USB-C port no configured as downstream
2020-12-11 Remove complicated zones on side not visible
2020-12-25 Update photo
2020-12-25 Swap images
2021-02-18 Make colors less confusing
2021-02-18 Fix: TX matched against TX, not RX
2021-02-18 Fix: Labels for RX/TX for male headers swapped
2021-02-18 Fix: RX needs to be connected to TX
2021-02-18 Preserve Unique IDs of connectors
2021-02-18 Refill
2021-02-18 Create separate fix for past design
2021-02-18 Remove temporary fix (ordered)
2021-02-19 Add sequencer example
2021-02-19 Fix: Durations colors upside down
2021-02-19 Add script for easy uploading
2021-02-19 Remove stray file from unrelated project
2021-02-19 Point to MiniCore
2021-02-19 Add noise wave form
2021-02-19 Debounce buttons
2021-02-19 Get rid of macros for LED config
2021-02-22 Mention not to put traces too close
2021-02-22 Add clearance to footprints without solder mask
2021-02-22 Mention value for clearance
2021-02-22 Move pads slightly inward, to match data sheet
2021-02-22 Shrink unnecessarily large clearance
2021-02-22 Reroute to accommodate larger clearance
2021-02-27 Illustrate sequencer example
2021-02-27 Fix: Wrong Markdown image syntax
2021-02-27 Reorganize directories
2021-02-27 Add atomic tree example
2021-02-27 Mention what buttons do
2021-02-27 Mention MiniCore globally
2021-02-27 Reduce to pentatonic scale
2021-02-27 Vary saturation in note colors
2021-03-03 Make it work w/ crossed over pins (correct wiring)
2021-03-03 Left align labels
2021-03-03 Update pinout to match cross over wiring
2021-03-03 Rewire to match schematic
2021-03-05 Match adapter colors and labels to that of an atom
2021-03-05 Swap yellow / green for lower board
2021-03-05 Fix RX/TX assignment lower board
2021-03-05 Swap RX/TX on lower board
2021-06-18 Fix video link
